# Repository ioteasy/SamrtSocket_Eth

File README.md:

# SamrtSocket_Eth
Socket controlled by GSM with Ethernet extension

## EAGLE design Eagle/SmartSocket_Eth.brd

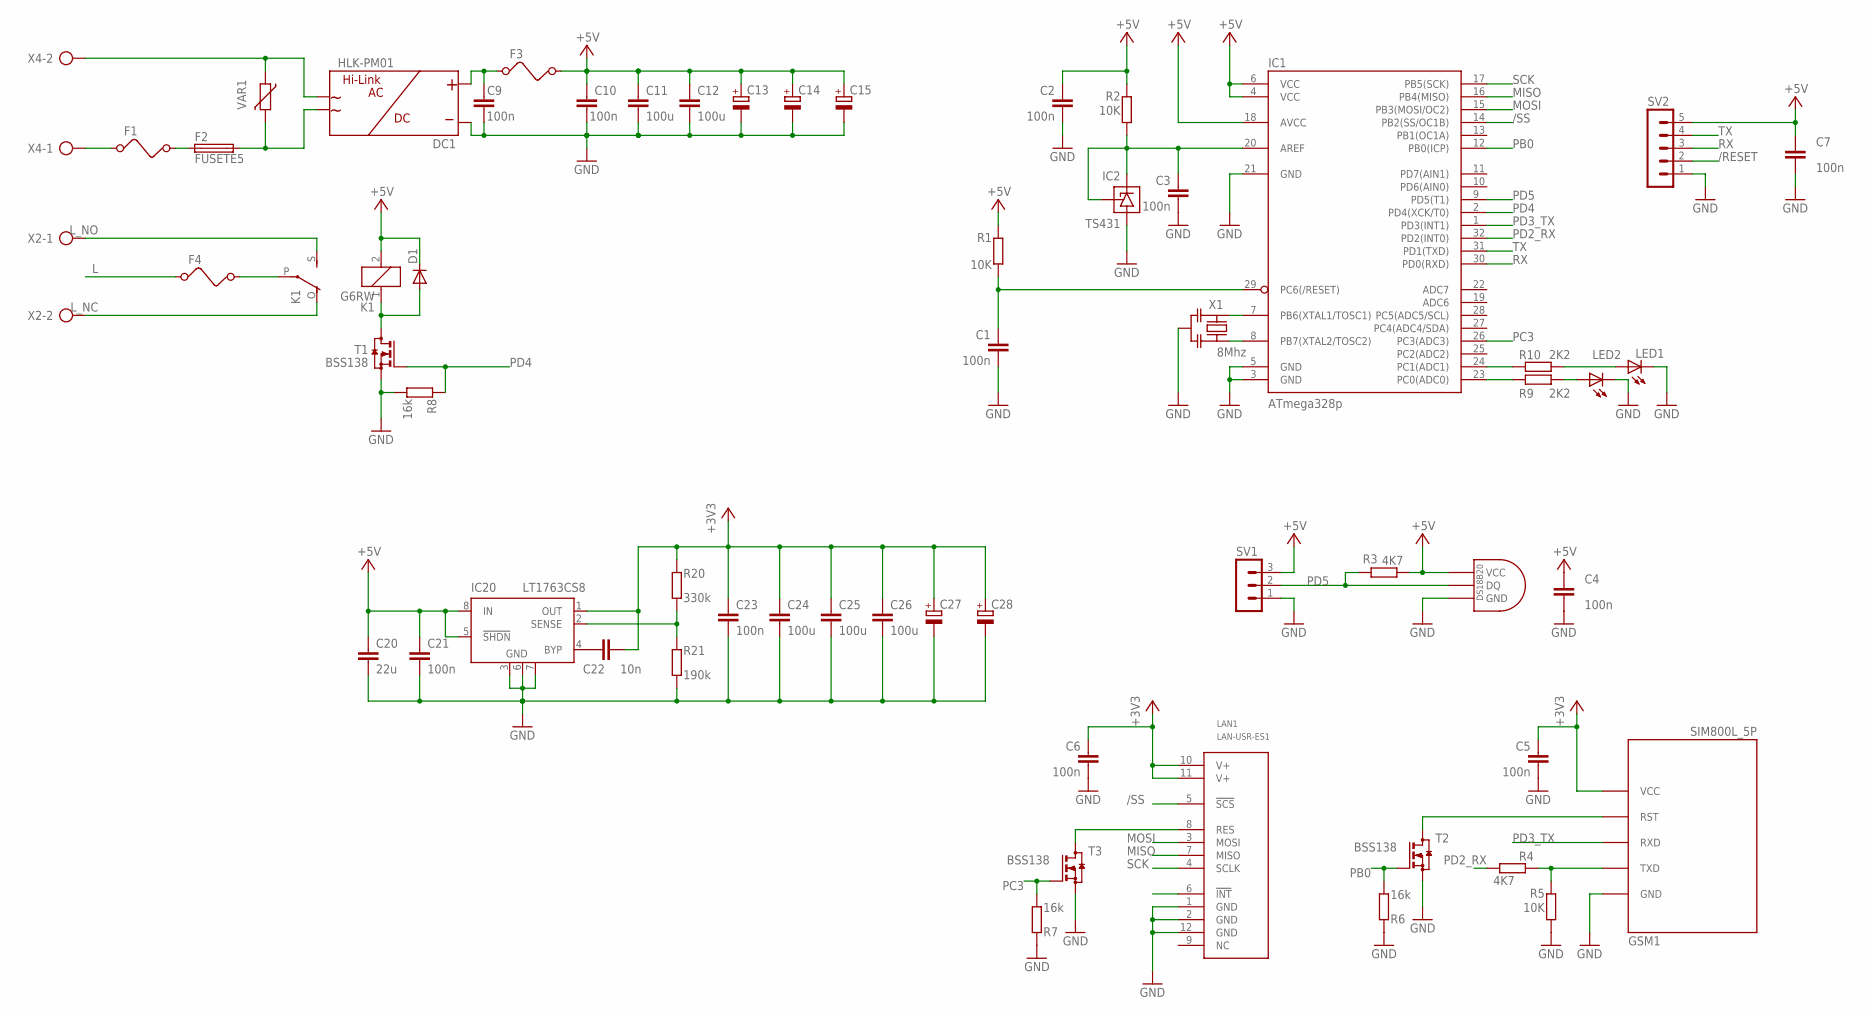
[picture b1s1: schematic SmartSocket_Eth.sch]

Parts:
18B20: DS1820TO92; DS1820
C1, C2, C3, C4, C5, C6, C7, C9, C10, C21: 100n; C0805
C11, C12, C24, C25, C26: 100u; C1206
C13: CPOL-EUE5-6; E5-6
C14, C15, C28: CPOL-EUSMCD; SMC_D
C20: 22u; C0805
C22: 10n; C0805
C23: 100n; C1206
C27: CPOL-EUE5-4; E5-4
D1: DIODE-MELF-MLL41; MELF-MLL41
DC1: HLK-PM01; HLK-3W
F1, F3, F4: FUSE
F2: FUSETE5; TE5
GSM1: SIM800L_5P
IC1: ATmega328p; TQFP32-08
IC2: TS431; SOT23
IC20: LT1763CS8; SOIC8
K1: G6RW
LAN1: LAN-USR-ES1; USR-ES1
LED1, LED2: LED3MM
R1, R2, R5: 10K; M0805
R3, R4: 4K7; M0805
R6, R7, R8: 16k; M0805
R9, R10: 2K2; M0805
R20: 330k; M0805
R21: 190k; M0805
SV1: MA03-1
SV2: MA05-1
T1, T2, T3: BSS138; SOT23
VAR1: VARISTORS07K40; S07K40
X1: 8Mhz; CERALOCK_CSTCE_G
X2, X4: AK500/2

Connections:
+3V3: C5.2, C6.2, C22.1, C23.1, C24.1, C25.1, C26.1, C27.+, C28.+, GSM1.P$1 (VCC), IC20.1 (OUT), LAN1.10 (V+), LAN1.11 (V+), R20.2
+5V: 18B20.VDD (VCC), C2.2, C4.2, C7.2, C10.2, C11.1, C12.1, C13.+, C14.+, C15.+, C20.1, C21.1, D1.C, F3.2, IC1.4 (VCC), IC1.6 (VCC), IC1.18 (AVCC), IC20.5 (!SHDN), IC20.8 (IN), K1.2, R1.2, R2.2, R3.2, SV1.3, SV2.5
/RESET: C1.2, IC1.29 (PC6(/RESET)), R1.1, SV2.2
/SS: IC1.14 (PB2(SS/OC1B)), LAN1.5 (!SCS!)
AREF: C3.2, IC1.20 (AREF), IC2.1 (REF), IC2.2 (C), R2.1
FB: IC20.2 (SENSE), R20.1, R21.2
GND: 18B20.GND, C1.1, C2.1, C3.1, C4.1, C5.1, C6.1, C7.1, C9.1, C10.1, C11.2, C12.2, C13.-, C14.-, C15.-, C20.2, C21.2, C23.2, C24.2, C25.2, C26.2, C27.-, C28.-, DC1.P$3, GSM1.P$5 (GND), IC1.3 (GND), IC1.5 (GND), IC1.21 (GND), IC2.3 (A), IC20.3 (GND), IC20.6 (GND), IC20.7 (GND), LAN1.1 (GND), LAN1.2 (GND), LAN1.12 (GND), LED1.K (C), LED2.K (C), R5.1, R6.1, R7.1, R8.2, R21.1, SV1.1, SV2.1, T1.2 (S), T2.2 (S), T3.2 (S), X1.P$2 (GND)
L: F1.1, F4.1, X4.1
L_NC: K1.O, X2.2
L_NO: K1.S, X2.1
MISO: IC1.16 (PB4(MISO)), LAN1.7 (MISO)
MOSI: IC1.15 (PB3(MOSI/OC2)), LAN1.3 (MOSI)
N: DC1.P$2, F2.2, VAR1.2
unnamed: DC1.P$1, VAR1.1, X4.2
unnamed: C9.2, DC1.P$4, F3.1
unnamed: F4.2, K1.P
unnamed: GSM1.P$2 (RST), T2.3 (D)
unnamed: LED1.A, R10.1
unnamed: LAN1.8 (RES), T3.3 (D)
unnamed: D1.A, K1.1, T1.3 (D)
unnamed: C22.2, IC20.4 (BYP)
unnamed: F1.2, F2.1
unnamed: IC1.8 (PB7(XTAL2/TOSC2)), X1.P$1 (1)
unnamed: IC1.7 (PB6(XTAL1/TOSC1)), X1.P$3 (2)
unnamed: LED2.A, R9.1
unnamed: GSM1.P$4 (TXD), R4.1, R5.2
PB0: IC1.12 (PB0(ICP)), R6.2, T2.1 (G)
PC0: IC1.23 (PC0(ADC0)), R9.2
PC1: IC1.24 (PC1(ADC1)), R10.2
PC3: IC1.26 (PC3(ADC3)), R7.2, T3.1 (G)
PD2_RX: IC1.32 (PD2(INT0)), R4.2
PD3_TX: GSM1.P$3 (RXD), IC1.1 (PD3(INT1))
PD4: IC1.2 (PD4(XCK/T0)), R8.1, T1.1 (G)
PD5: 18B20.DQ, IC1.9 (PD5(T1)), R3.1, SV1.2
RX: IC1.30 (PD0(RXD)), SV2.3
SCK: IC1.17 (PB5(SCK)), LAN1.4 (SCLK)
TX: IC1.31 (PD1(TXD)), SV2.4

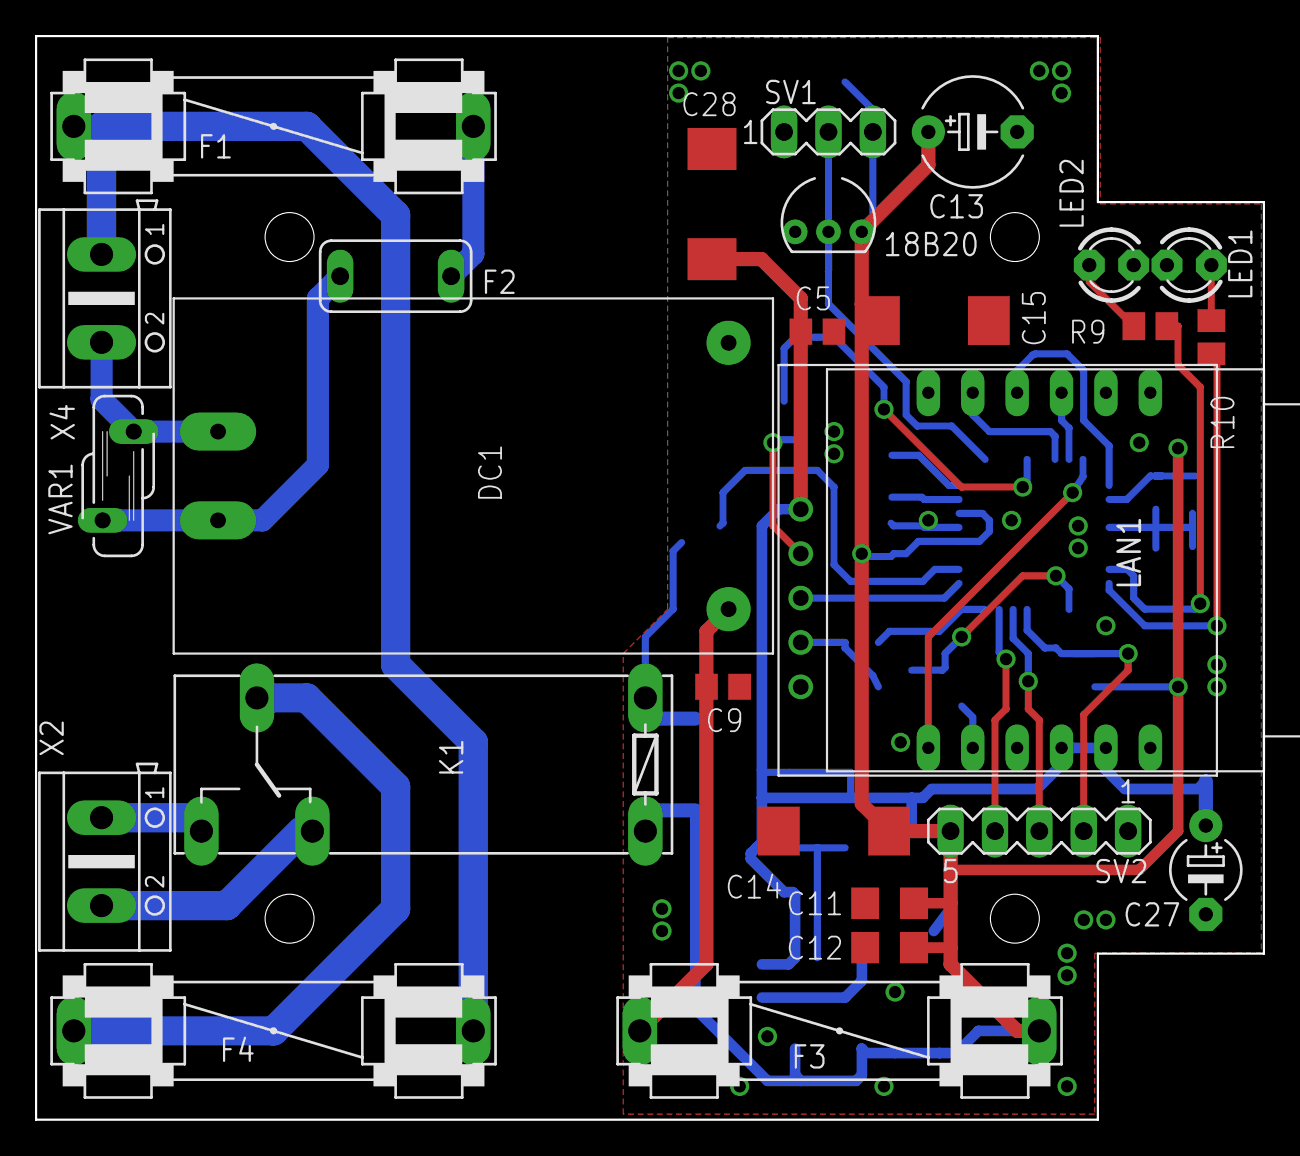
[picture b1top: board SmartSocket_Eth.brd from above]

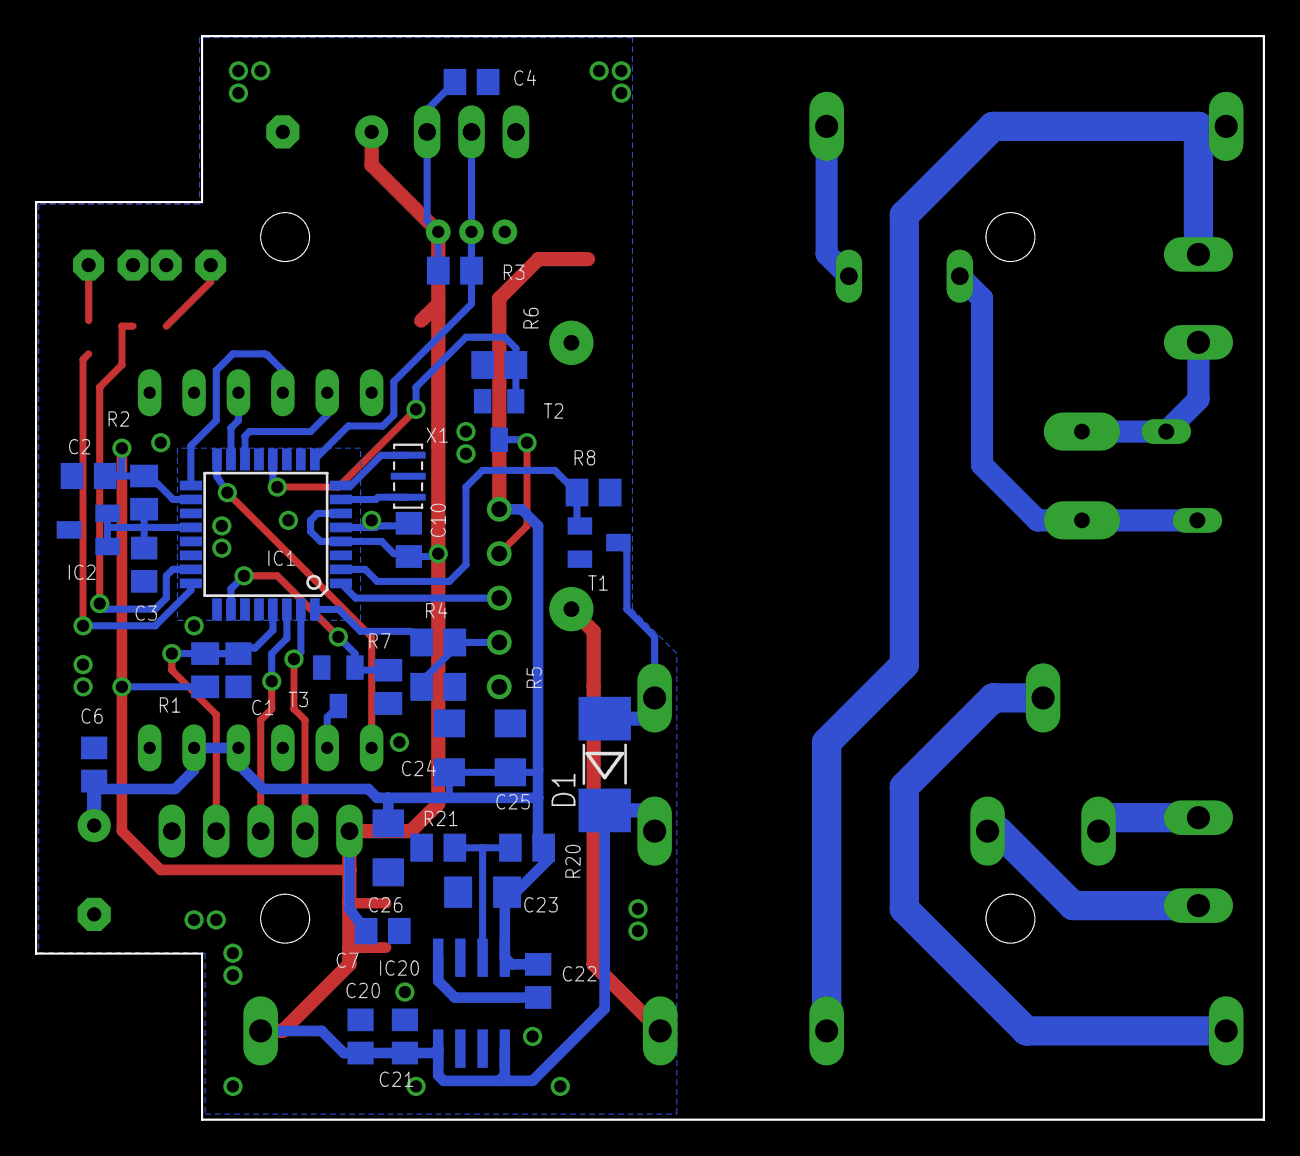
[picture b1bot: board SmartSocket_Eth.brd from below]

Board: 2 copper layers, 70.3 x 62.0 mm, 60 parts (32 on the bottom side), 37 nets.

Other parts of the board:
U$1: Z27
